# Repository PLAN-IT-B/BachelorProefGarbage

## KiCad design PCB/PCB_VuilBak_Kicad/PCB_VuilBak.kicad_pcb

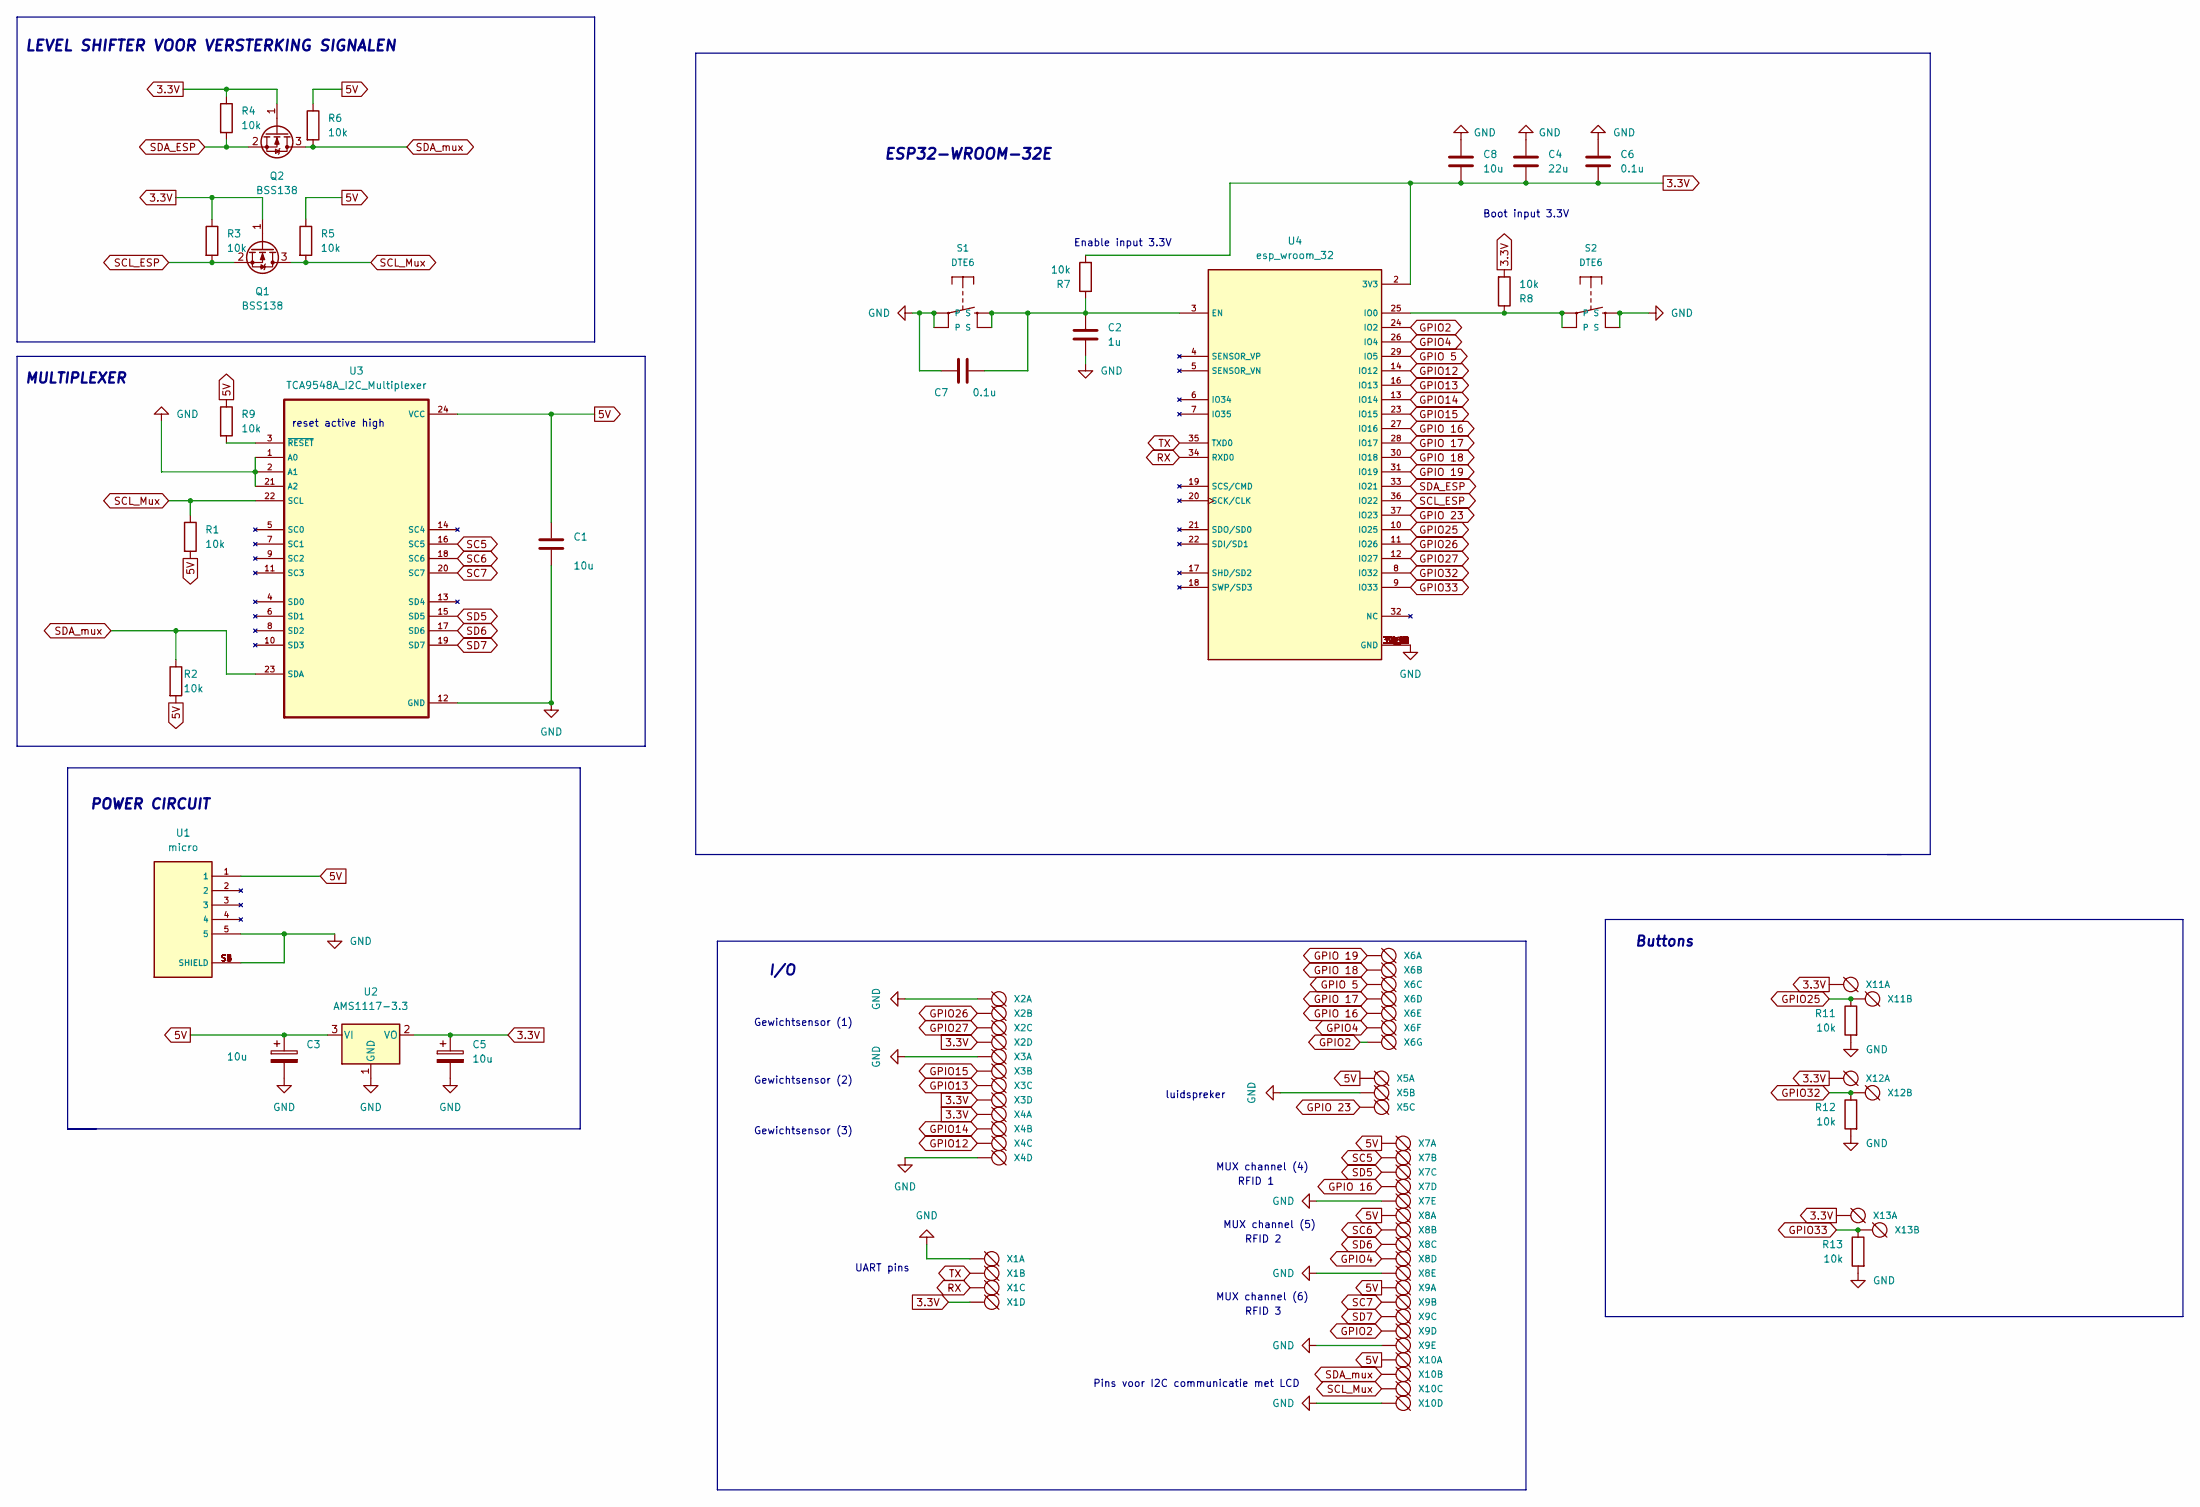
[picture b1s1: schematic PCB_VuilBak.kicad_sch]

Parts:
C1, C3, C5, C8: 10u; C_0805_2012Metric
C2: 1u; C_0805_2012Metric
C4: 22u; C_0805_2012Metric
C6, C7: 0.1u; C_0805_2012Metric
Q1, Q2: BSS138; SOT-23
R1, R2, R3, R4, R5, R6, R7, R8, R9, R11, R12, R13: 10k; C_0805_2012Metric
S1, S2: DTE6; TE_1-1825910-4
U1: micro; MOLEX_105017-1001
U2: AMS1117-3.3; SOT-223-3_TabPin2
U3: TCA9548A_I2C_Multiplexer; SOP65P640X120-24N
U4: esp_wroom_32; MODULE_ESP32-WROOM-32
X1, X2, X3, X4, X10: DG3XX-04-3.5; PinHeader_1x04_P2.54mm_Vertical
X5: DG3XX-03-3.5; PinHeader_1x03_P2.54mm_Vertical
X6: DG3XX-07-3.5; PinHeader_1x07_P2.54mm_Vertical
X7, X8, X9: DG3XX-05-3.5; PinHeader_1x05_P2.54mm_Vertical
X11, X12, X13: DG3XX-02-3.5; PinHeader_1x02_P2.54mm_Vertical

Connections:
3.3V: C4.2, C5.1, C6.2, C8.2, Q1.1 (G), Q2.1 (G), R3.1, R4.1, R7.2, R8.2, U2.2 (VO), U4.2 (3V3), X1.4 (KL), X2.4 (KL), X3.4 (KL), X4.1 (KL), X11.1 (KL), X12.1 (KL), X13.1 (KL)
5V: C1.2, C3.1, R1.2, R2.2, R5.1, R6.1, R9.1, U1.1, U2.3 (VI), U3.24 (VCC), X5.1 (KL), X7.1 (KL), X8.1 (KL), X9.1 (KL), X10.1 (KL)
GND: C1.1, C2.2, C3.2, C4.1, C5.2, C6.1, C7.1, C8.1, R11.2, R12.2, R13.2, S1.3, S1.4, S2.1 (S), S2.2 (S), U1.5, U1.S1 (SHIELD), U1.S2 (SHIELD), U1.S3 (SHIELD), U1.S4 (SHIELD), U1.S5 (SHIELD), U1.S6 (SHIELD), U2.1 (GND), U3.1 (A0), U3.2 (A1), U3.12 (GND), U3.21 (A2), U4.1 (GND), U4.15 (GND), U4.38 (GND), U4.39_1 (GND), U4.39_2 (GND), U4.39_3 (GND), U4.39_4 (GND), U4.39_5 (GND), U4.39_6 (GND), U4.39_7 (GND), U4.39_8 (GND), U4.39_9 (GND), U4.39_10 (GND), U4.39_11 (GND), U4.39_12 (GND), U4.39_13 (GND), U4.39_14 (GND), U4.39_15 (GND), U4.39_16 (GND), U4.39_17 (GND), U4.39_18 (GND), U4.39_19 (GND), U4.39_20 (GND), U4.39_21 (GND), X1.1 (KL), X2.1 (KL), X3.1 (KL), X4.4 (KL), X5.2 (KL), X7.5 (KL), X8.5 (KL), X9.5 (KL), X10.4 (KL)
GPIO2: U4.24 (IO2), X6.7 (KL), X9.4 (KL)
GPIO4: U4.26 (IO4), X6.6 (KL), X8.4 (KL)
GPIO12: U4.14 (IO12), X4.3 (KL)
GPIO13: U4.16 (IO13), X3.3 (KL)
GPIO14: U4.13 (IO14), X4.2 (KL)
GPIO15: U4.23 (IO15), X3.2 (KL)
GPIO25: R11.1, U4.10 (IO25), X11.2 (KL)
GPIO26: U4.11 (IO26), X2.2 (KL)
GPIO27: U4.12 (IO27), X2.3 (KL)
GPIO32: R12.1, U4.8 (IO32), X12.2 (KL)
GPIO33: R13.1, U4.9 (IO33), X13.2 (KL)
GPIO 5: U4.29 (IO5), X6.3 (KL)
GPIO 16: U4.27 (IO16), X6.5 (KL), X7.4 (KL)
GPIO 17: U4.28 (IO17), X6.4 (KL)
GPIO 18: U4.30 (IO18), X6.2 (KL)
GPIO 19: U4.31 (IO19), X6.1 (KL)
GPIO 23: U4.37 (IO23), X5.3 (KL)
unnamed: C2.1, C7.2, R7.1, S1.1 (S), S1.2 (S), U4.3 (EN)
unnamed: R8.1, S2.3, S2.4, U4.25 (IO0)
unnamed: R9.2, U3.3 (~RESET)
RX: U4.34 (RXD0), X1.3 (KL)
SC5: U3.16 (SC5), X7.2 (KL)
SC6: U3.18 (SC6), X8.2 (KL)
SC7: U3.20 (SC7), X9.2 (KL)
SCL_ESP: Q1.2 (S), R3.2, U4.36 (IO22)
SCL_Mux: Q1.3 (D), R1.1, R5.2, U3.22 (SCL), X10.3 (KL)
SD5: U3.15 (SD5), X7.3 (KL)
SD6: U3.17 (SD6), X8.3 (KL)
SD7: U3.19 (SD7), X9.3 (KL)
SDA_ESP: Q2.2 (S), R4.2, U4.33 (IO21)
SDA_mux: Q2.3 (D), R2.1, R6.2, U3.23 (SDA), X10.2 (KL)
TX: U4.35 (TXD0), X1.2 (KL)

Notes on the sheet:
RFID 2
ESP32-WROOM-32E
Gewichtsensor (3)
Pins voor I2C communicatie met LCD
reset active high
Enable input 3.3V
Gewichtsensor (1)
RFID 3
RFID 1
Boot input 3.3V
luidspreker
Gewichtsensor (2)
MUX channel (5)
MUX channel (4)
LEVEL SHIFTER VOOR VERSTERKING SIGNALEN
I/O
POWER CIRCUIT
MULTIPLEXER
MUX channel (6)
Buttons
UART pins

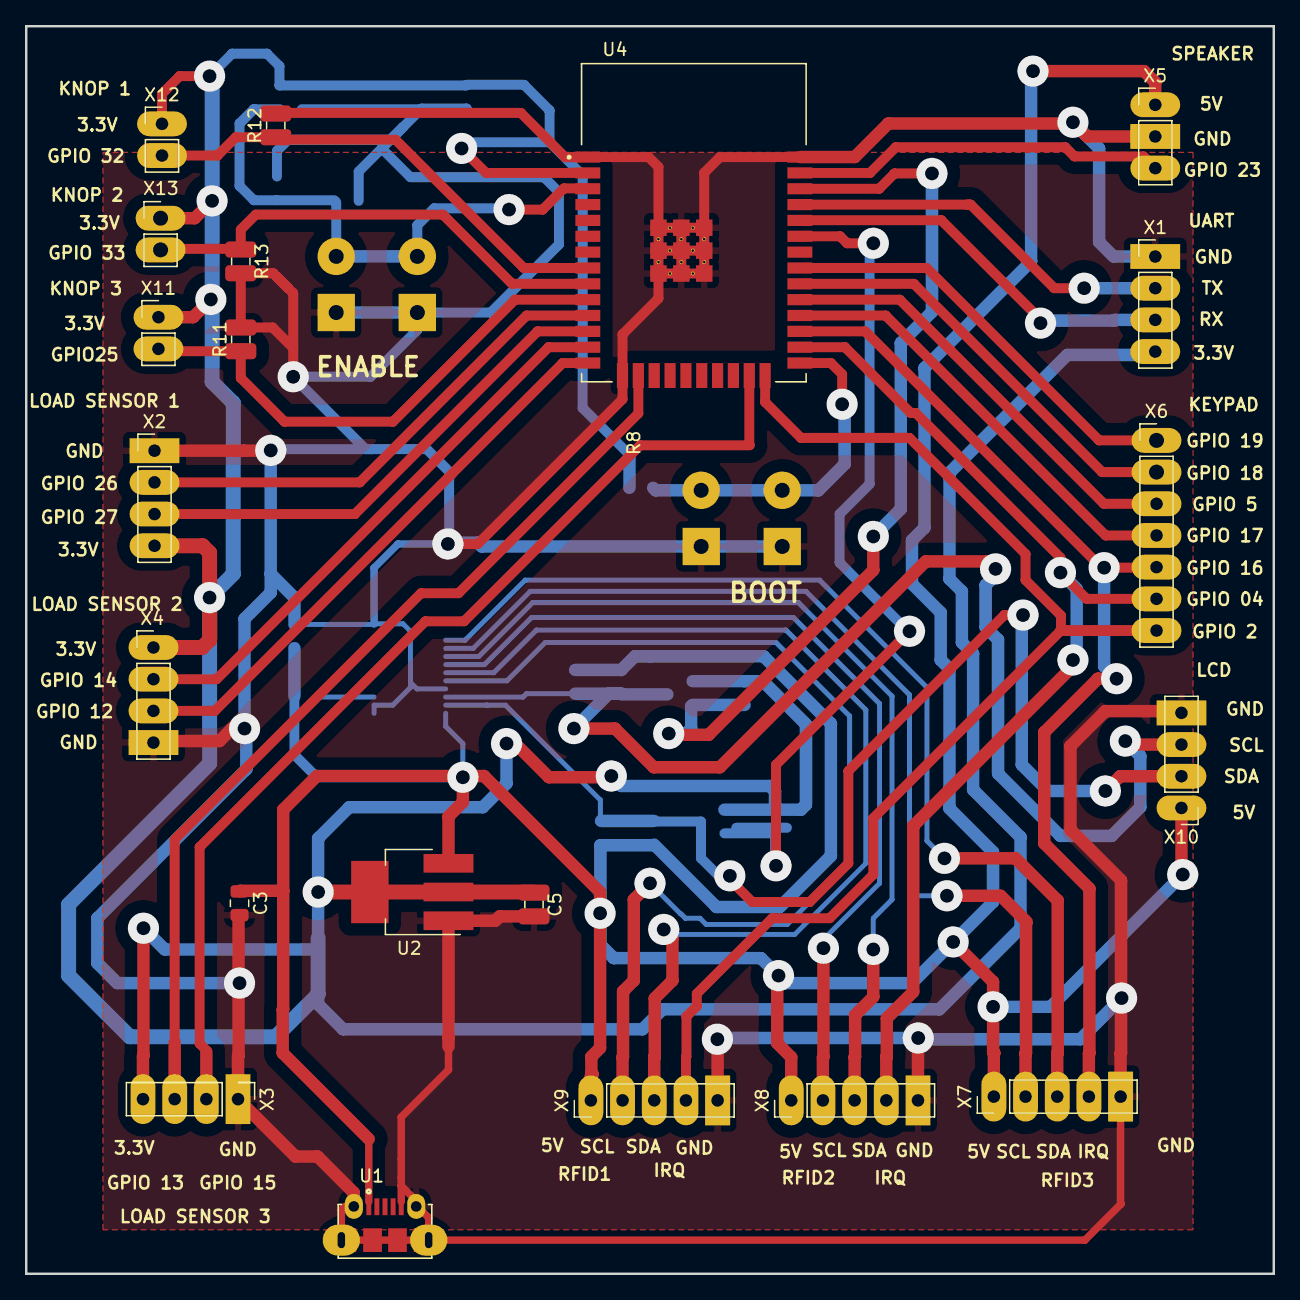
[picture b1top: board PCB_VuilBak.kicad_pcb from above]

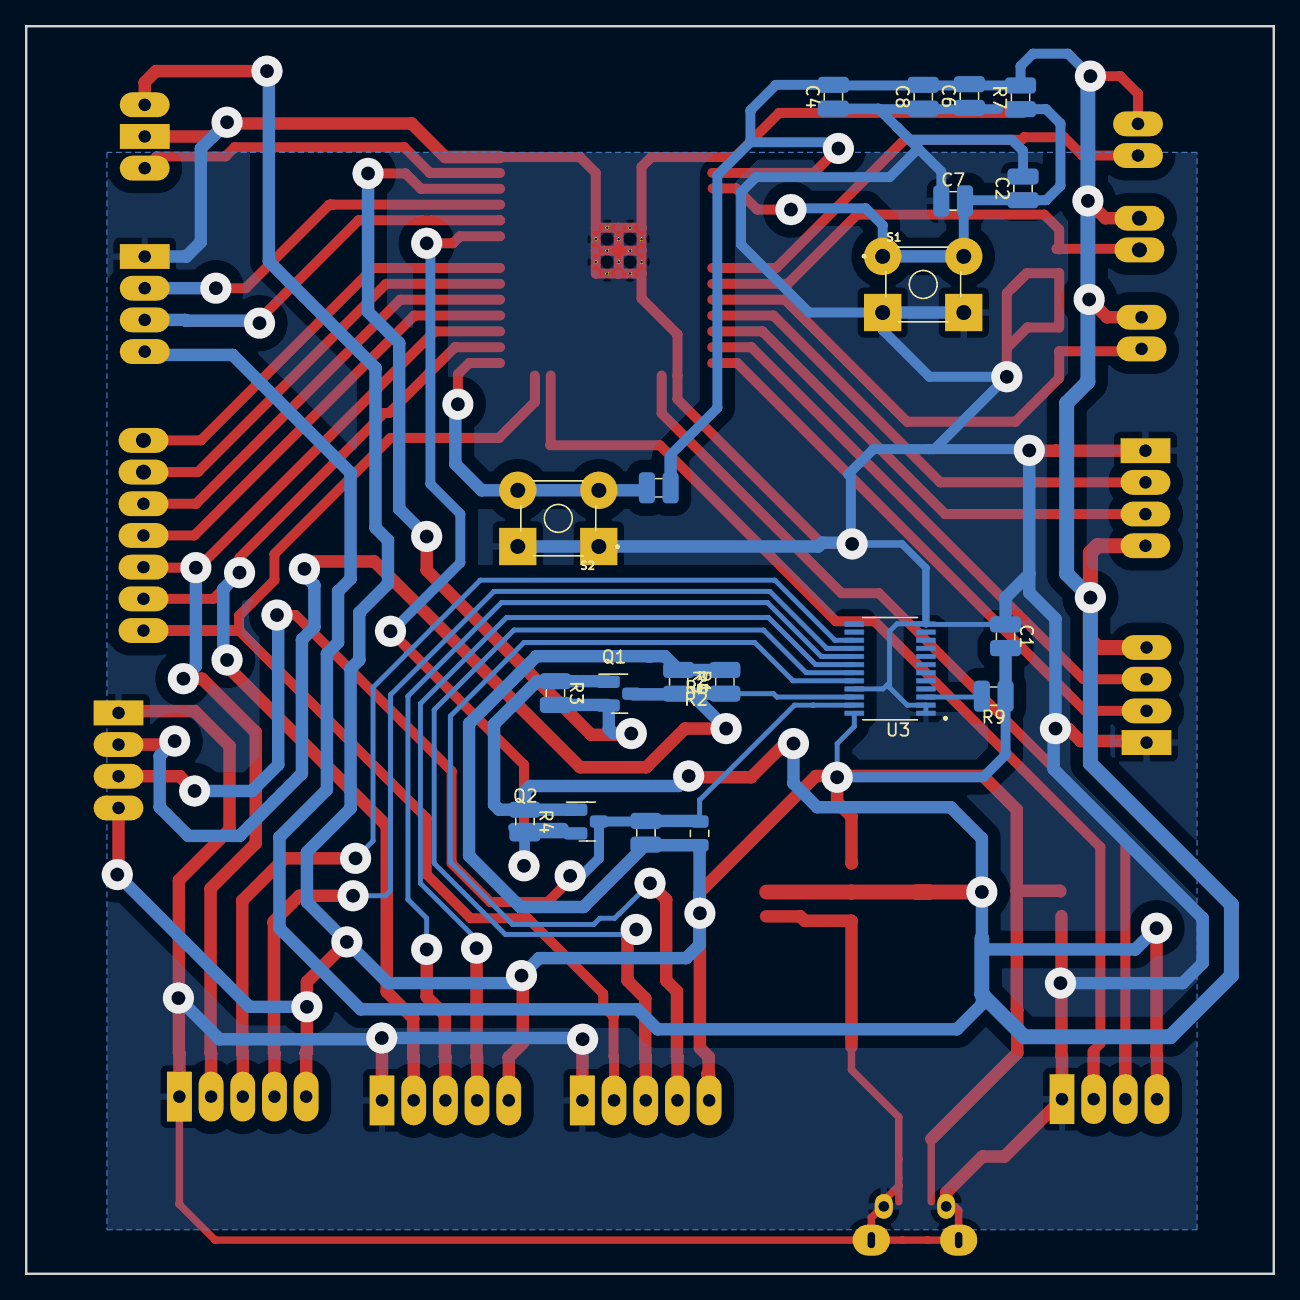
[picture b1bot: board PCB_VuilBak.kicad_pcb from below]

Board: 2 copper layers, 100.0 x 100.0 mm, 41 parts (20 on the bottom side), 35 nets.

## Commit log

2022-02-16 Create RFIDTest(main).cpp
    Test file RFID
2022-02-16 LCD + I2C
    - Voorbeeld voor aansturen LCD
    - Voorbeeld voor achterhalen I2C adres module
2022-02-21 planning BAP
    planning gemaakt met gantt chart
2022-02-21 planning aangepast
2022-02-21 Create Eerste ontwerp vuilbakken.docx
    Eerste ontwerp toegevoegd
2022-02-21 Update word ontwerp vuilbakken
    Update
2022-02-21 Blokschema toegevoegd
2022-02-21 Create BOM.docx
    BOM toegevoegd (Heel algemeen)
2022-02-22 typfout verbeterd
2022-02-22 Create Blokschema_vuilbak.pdf
    blokschema puzzel
2022-02-22 samenvatting puzzel in appart doc gezet
2022-02-22 blokschema aangepast
2022-02-22 Update BOM.docx
    Update bom
2022-02-22 Create SterktesZwaktes.docx
    Sterktes en zwakter erin zetten
2022-02-22 networking example (pass-generator)
2022-02-23 Aanpassen SWOT
2022-02-23 Aanpassing swot
2022-02-24 Update BOM.docx
    Kleine aanpassing (Op school erbij gezet)
2022-02-26 Toevoegen netwerk-rfid-mqtt
    Dit programma zal handig zijn voor onze finale code
2022-02-28 Aanpassing bom/organiseren
2022-02-28 3x4 keypad van op digikey erbij gezet
2022-03-01 added projectweek workshop 1
2022-03-01 Toevoegen code
2022-03-01 Bezig met lcd
2022-03-01 final bom gemaakt
2022-03-07 Becommentarieren + kleine aanpassingen lcd
2022-03-08 Functies maken
2022-03-08 Opruimen en RFID
2022-03-08 dqfgq
2022-03-15 cleaning
2022-03-15 callibratie load sensors toefevoegd
2022-03-15 Keypad werkend
2022-03-22 verder gewerkt aan PCB
2022-03-22 pcb schema updated
2022-03-22 Add multiplex test
2022-03-22 update pcb-schema
2022-03-29 Geluidjes toegevoegd
2022-03-29 Juiste codes worden verwijderd
2022-04-03 update pcb
2022-04-03 pcb update
2022-04-07 Einde week
2022-04-12 zip maken
2022-04-14 Adding ground plane
2022-04-14 last check
2022-04-19 loadsensor update
2022-04-19 gewicht
2022-04-26 update main
2022-04-27 laser-cut files toegevoegd
2022-05-02 Niets aangepast
2022-05-03 gpio change
2022-05-03 update gpio
2022-05-04 update test your buddy
2022-05-05 Test
2022-05-12 Definitief main
2022-05-16 Updat main
2022-05-18 update schema
    update schema voor documentatie
2022-05-19 Aanmaken code
2022-05-21 tekst toegevoegd
